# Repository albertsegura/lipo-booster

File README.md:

# lipo-booster

Power board charges LIPO battery at 1000mA from USB, supplies 5V @ 2A with load sharing.

Based on Adafruit [PowerBooster 1000c](https://www.adafruit.com/product/2465) but featuring hand-solderable ICs!

Features:
* LIPO Charger Controller Microchip [MCP73833](http://ww1.microchip.com/downloads/en/DeviceDoc/22005b.pdf)
* Synchronous Boost Converter Texas Instrument [TPS61032](http://www.ti.com/lit/ds/symlink/tps61032.pdf)
* Load Sharing Circuit based on Microchip [AN1149](http://ww1.microchip.com/downloads/en/appnotes/01149c.pdf)

<div>

</div>

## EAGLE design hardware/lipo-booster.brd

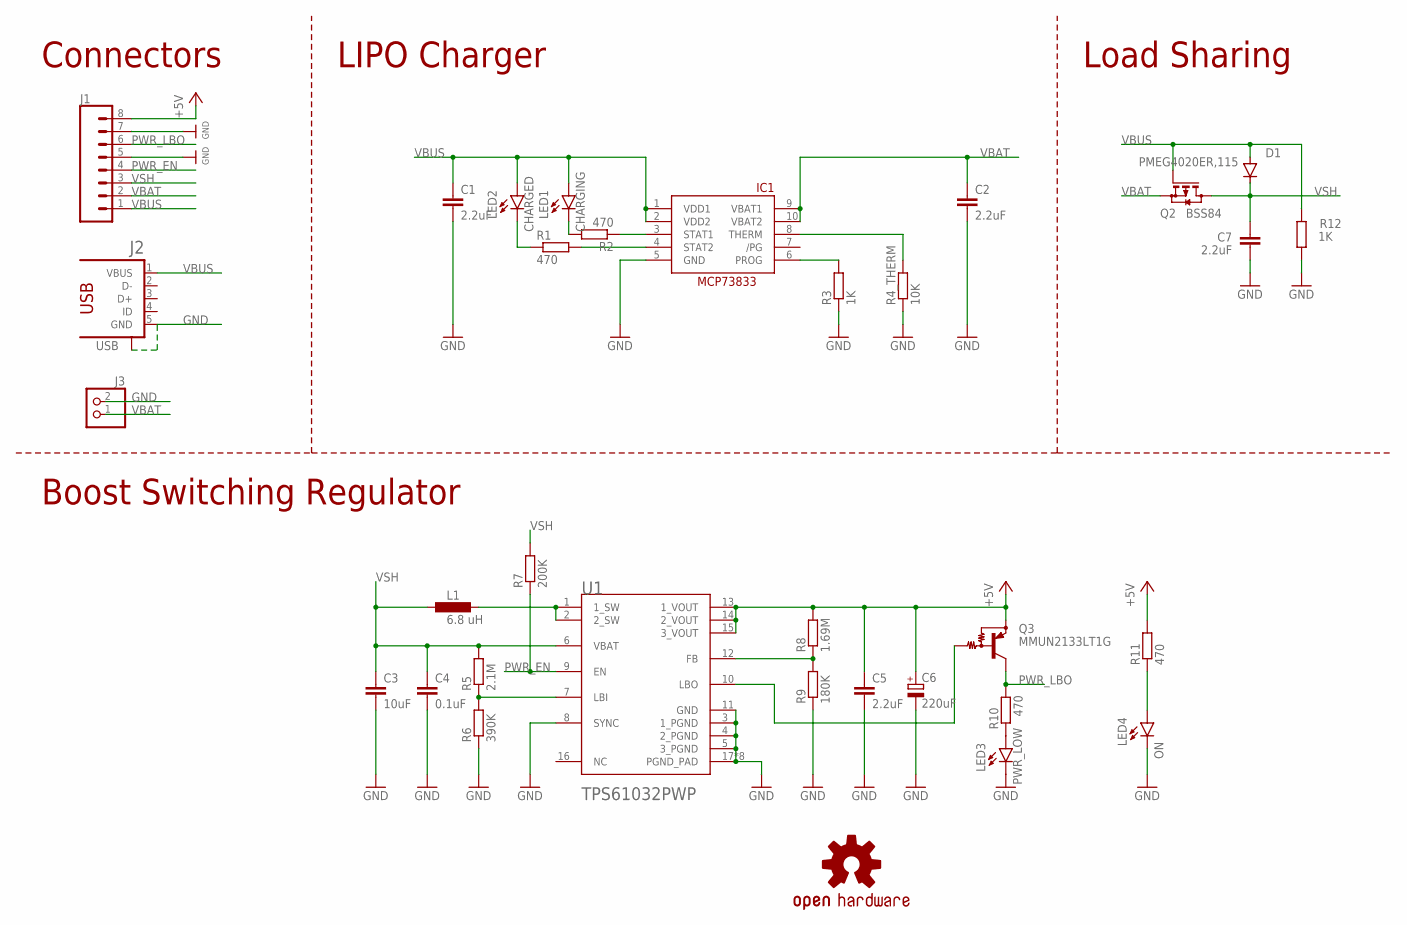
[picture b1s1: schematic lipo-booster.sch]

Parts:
C1, C2, C5, C7: 2.2uF; C0603
C3: 10uF; C0603
C4: 0.1uF; C0603
C6: 220uF; CT3528
D1: PMEG4020ER,115; SOD-123_MINI-SMA
IC1: MCP73833-UN; MSOP10
J1: CONN_08"; 1X08
J2: USB; 1981584-1
J3: JST_2PIN-THM; JST-PH-2-THM
L1: 6.8 uH; POWER-CHOKE_WE-TPC
LED1: CHARGING; CHIP-LED0603
LED2: CHARGED; CHIP-LED0603
LED3: PWR_LOW; CHIP-LED0603
LED4: ON; CHIP-LED0603
LOGO1: OSHW-LOGOS; OSHW-LOGO-S
Q2: BSS84; SOT23
Q3: MMUN2133LT1G; SC59-BEC
R1, R2, R10, R11: 470; R0603
R3, R12: 1K; R0603
R4_THERM: 10K; R0603
R5: 2.1M; R0603
R6: 390K; R0603
R7: 200K; R0603
R8: 1.69M; R0603
R9: 180K; R0603
U1: TEXAS_INSTRUMENTS_TPS61032PWPTEXAS_INSTRUMENTS_TP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; TEXAS_INSTRUMENTS_TPS61032PWP_0

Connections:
+5V: C5.1, C6.- (+), J1.8, Q3.E, R8.2, R11.2, U1.13 (1_VOUT), U1.14 (2_VOUT), U1.15 (3_VOUT)
GND: C1.2, C2.2, C3.2, C4.2, C5.2, C6.+ (-), C7.2, IC1.5 (GND), J1.5, J1.7, J2.5 (GND), J2.S1, J3.2 (1), LED3.C, LED4.C, R3.1, R4_THERM.1, R6.1, R9.1, R12.1, U1.3 (1_PGND), U1.4 (2_PGND), U1.5 (3_PGND), U1.8 (SYNC), U1.11 (GND), U1.17 (PGND_PAD), U1.PAD_1 (PGND_PAD), U1.PAD_2 (PGND_PAD), U1.PAD_3 (PGND_PAD), U1.PAD_4 (PGND_PAD), U1.PAD_5 (PGND_PAD), U1.PAD_6 (PGND_PAD), U1.SMD_33 (PGND_PAD)
unnamed: L1.1, U1.1 (1_SW), U1.2 (2_SW)
unnamed: LED4.A, R11.1
unnamed: LED3.A, R10.1
unnamed: IC1.8 (THERM), R4_THERM.2
unnamed: IC1.3 (STAT1), R2.1
unnamed: IC1.4 (STAT2), R1.2
unnamed: LED1.C, R2.2
unnamed: IC1.6 (PROG), R3.2
unnamed: LED2.C, R1.1
unnamed: R5.1, R6.2, U1.7 (LBI)
unnamed: Q3.B, U1.10 (LBO)
unnamed: R8.1, R9.2, U1.12 (FB)
PWR_EN: J1.4, R7.1, U1.9 (EN)
PWR_LBO: J1.6, Q3.C, R10.2
VBAT: C2.1, IC1.9 (VBAT1), IC1.10 (VBAT2), J1.2, J3.1 (2), Q2.2 (S)
VBUS: C1.1, D1.A, IC1.1 (VDD1), IC1.2 (VDD2), J1.1, J2.1 (VBUS), LED1.A, LED2.A, Q2.1 (G), R12.2
VSH: C3.1, C4.1, C7.1, D1.C, J1.3, L1.2, Q2.3 (D), R5.2, R7.2, U1.6 (VBAT)

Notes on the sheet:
LIPO Charger
Load Sharing
Boost Switching Regulator
Connectors

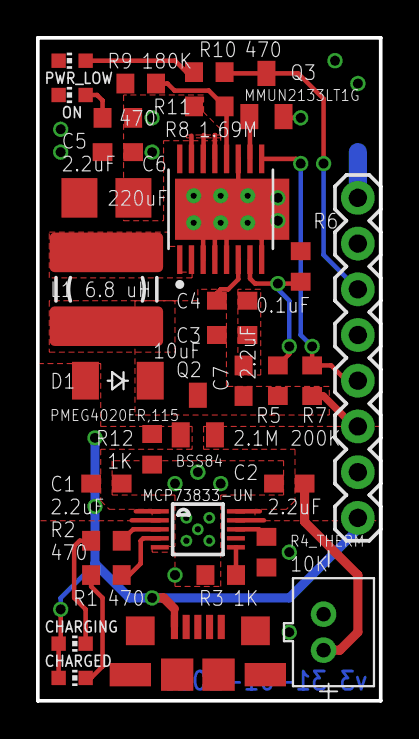
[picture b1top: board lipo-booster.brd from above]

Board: 2 copper layers, 19.1 x 36.8 mm, 33 parts (1 on the bottom side), 19 nets.

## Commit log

2019-01-27 Added aditional resources ORganized directories
2019-01-27 Added schematics svg
2019-01-27 Changes image
2019-02-05 Updated design with pcb layout suggestions from reddit thread
2019-02-24 Small change to schematic to change transistor and update of photo

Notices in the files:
parts and their libraries:
SparkFun-Aesthetics: Licensing: CC v3.0 Share-Alike You are welcome to use this library for commercial purposes.
SparkFun-Connectors: Licensing: Creative Commons ShareAlike 4.0 International - https://creativecommons.org/licenses/by-sa/4.0
